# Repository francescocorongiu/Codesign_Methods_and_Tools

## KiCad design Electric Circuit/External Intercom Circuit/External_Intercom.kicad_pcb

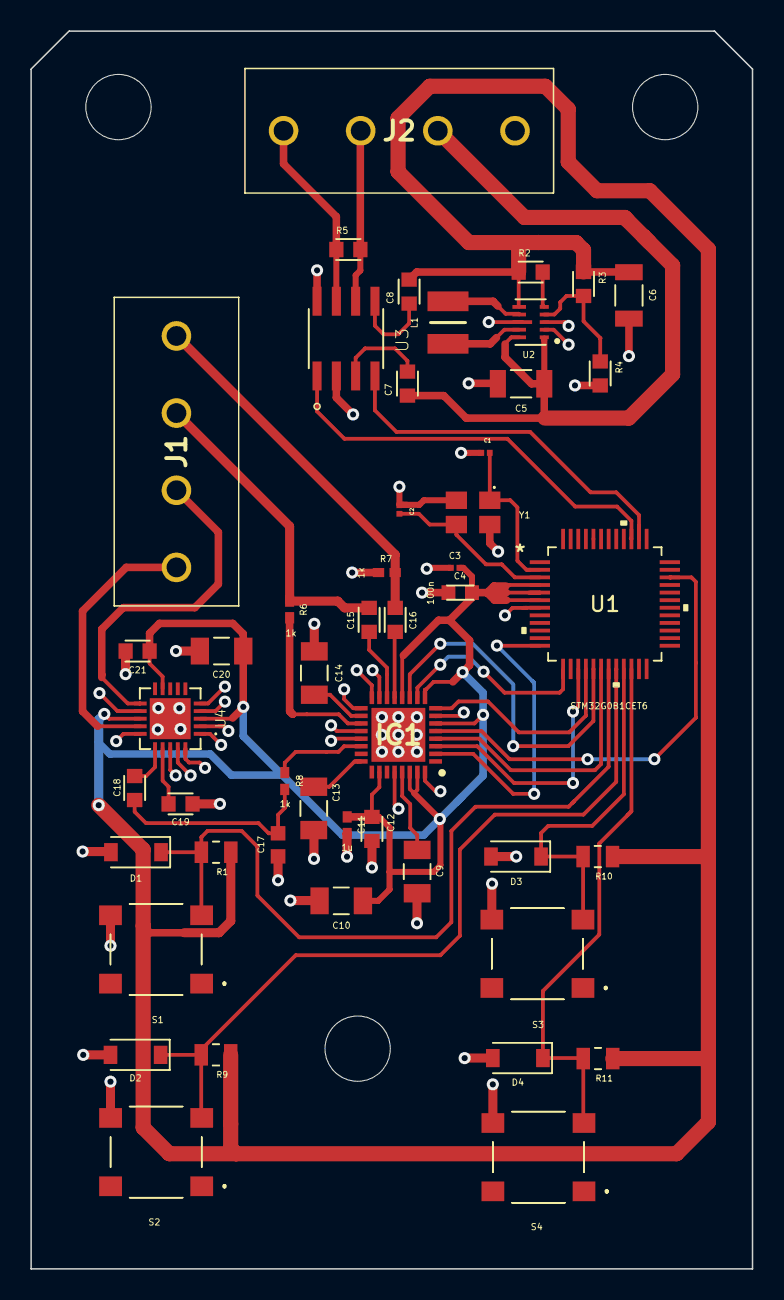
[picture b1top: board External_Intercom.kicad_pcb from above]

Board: 2 copper layers, 47.5 x 81.5 mm, 52 parts (0 on the bottom side), 40 nets.

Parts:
C1, C2: 20p; RESC0603X26N
C3: 4.7u; RESC0603X26N
C4: 100n; CAPC1608X90N
C5, C6: 22u; RESC1206X70N
C7, C8, C12, C15, C16, C18, C19, C21: 0.1u; RESC1608X50N
C9, C10, C13, C14, C20: 10u; CAPC3216X180N
C11: 1u; RESC1005X40N
C17: 4.7n; CAPC1608X95N
D1, D2, D3, D4: MMSZ2V7T1G; D_SOD-123
H2, H3, H4: MountingHole; MountingHole_4.3mm_M4
IC1: TLV320AIC3254IRHBT; QFN50P500X500X100-33N-D
J1, J2: TB006-508-04BE; TB00650804BE
L1: 470n; INDC3225X120N
R1, R9, R10, R11: 13k; RESC2012X60N
R2: 100k; RESC1608X50N
R3: 511k; RESC1608X50N
R4: 91k; RESC1608X50N
R5: 120; RESC1608X50N
R6, R7, R8: 1k; RESC1005X40N
S1, S2, S3, S4: PTS645SK50JSMTR92_LFS; PTS645SK50JSMTR92LFS
U1: STM32G0B1CET6
U2: TPS63802DLAR; VREG_TPS63802DLAR
U3: MCP2542FD-H_SN; SOIC127P600X175-8N
U4: TPA2012D2RTJT; QFN50P400X400X80-21N270X270
Y1: TSX-322524.0000MF15X-AC3; TSX3225240000MF15XAC3

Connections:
/CAN_Transceiver/CANH: J2.4, R5.1, U3.7
/CAN_Transceiver/CANL: J2.3, R5.2, U3.6
/CAN_Transceiver/VDD: C5.1, C7.1, J2.2, U2.1, U2.10
/Codec_Subsystem/BCLK: IC1.2, U1.12
/Codec_Subsystem/DIN: IC1.4, U1.18
/Codec_Subsystem/DOUT: IC1.5, U1.34
/Codec_Subsystem/MIC_NEG: C16.2, J1.4, R7.1
/Codec_Subsystem/MIC_POS: C15.2, J1.3, R6.2
/Codec_Subsystem/MISO: IC1.11, U1.17
/Codec_Subsystem/MOSI: IC1.10, U1.13
/Codec_Subsystem/SP_OUT+: J1.1, U4.14
/Codec_Subsystem/SP_OUT-: J1.2, U4.11
/Codec_Subsystem/VDD: C3.1, C4.1, C6.1, C8.2, C10.1, C11.1, C12.1, C20.1, C21.1, IC1.6, IC1.9, IC1.12, IC1.26, IC1.30, IC1.31, R1.1, R2.1, R3.1, R9.1, R10.1, R11.1, U1.4, U1.5, U1.6, U2.6, U4.3, U4.9, U4.13
/Codec_Subsystem/kicad_schematic_speaker/LO: IC1.22, R8.2
/Codec_Subsystem/mic_conditioner/IN_L: C16.1, IC1.13
/Codec_Subsystem/mic_conditioner/IN_R: C15.1, IC1.14
/Codec_Subsystem/mic_conditioner/MICBIAS: IC1.19, R6.1
/Microcontroller_Subsystem/PA4: IC1.3, U1.15
/Microcontroller_Subsystem/PA5: IC1.8, U1.16
/Microcontroller_Subsystem/PD0: U1.38, U3.4
/Microcontroller_Subsystem/PD1: U1.39, U3.1
/sheet60D19BB9/C1: D1.1, R1.2, S1.C1, U1.19
/sheet60D324D3/C1: D2.1, R9.2, S2.C1, U1.20
/sheet60D3257E/C1: D3.1, R10.2, S3.C1, U1.21
/sheet60D32761/C1: D4.1, R11.2, S4.C1, U1.22
GND: C1.1, C2.1, C3.2, C4.2, C5.2, C6.2, C9.2, C10.2, C11.2, C12.2, C13.2, C14.2, C17.2, C19.1, C20.2, C21.2, D1.2, D2.2, D3.2, D4.2, IC1.7, IC1.15, IC1.16, IC1.17, IC1.20, IC1.21, IC1.28, IC1.32, IC1.33, J2.1, R4.2, R7.2, S1.D1, S2.D1, S3.D1, S4.D1, U1.7, U2.2, U2.3, U2.8, U3.2, U3.8, U4.1, U4.2, U4.4, U4.5, U4.12, U4.15, U4.18, U4.19, U4.20, U4.21, Y1.2, Y1.4
unnamed: C1.2, U1.2, Y1.1
unnamed: C2.2, U1.3, Y1.3
unnamed: C7.2, U3.3
unnamed: C8.1, U3.5
unnamed: C9.1, IC1.29
unnamed: C13.1, IC1.24
unnamed: C14.1, IC1.18
unnamed: C17.1, C18.1, R8.1
unnamed: C18.2, U4.16
unnamed: C19.2, U4.17
unnamed: L1.1, U2.9
unnamed: L1.2, U2.7
unnamed: R2.2, U2.5
unnamed: R3.2, R4.1, U2.4

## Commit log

2021-06-27 Intercom
2021-06-27 visual paradigm
